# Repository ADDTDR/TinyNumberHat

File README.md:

# TinyNumberHat 

<!-- 

  -->

Red ALS314         |  Green AL304V 
:-------------------------:|:-------------------------:
  |  
                                                | 
<hr>
Clock example

<!-- # Build  -->

<!--img src="images/IMG_4520.jpeg" width="400"/-->

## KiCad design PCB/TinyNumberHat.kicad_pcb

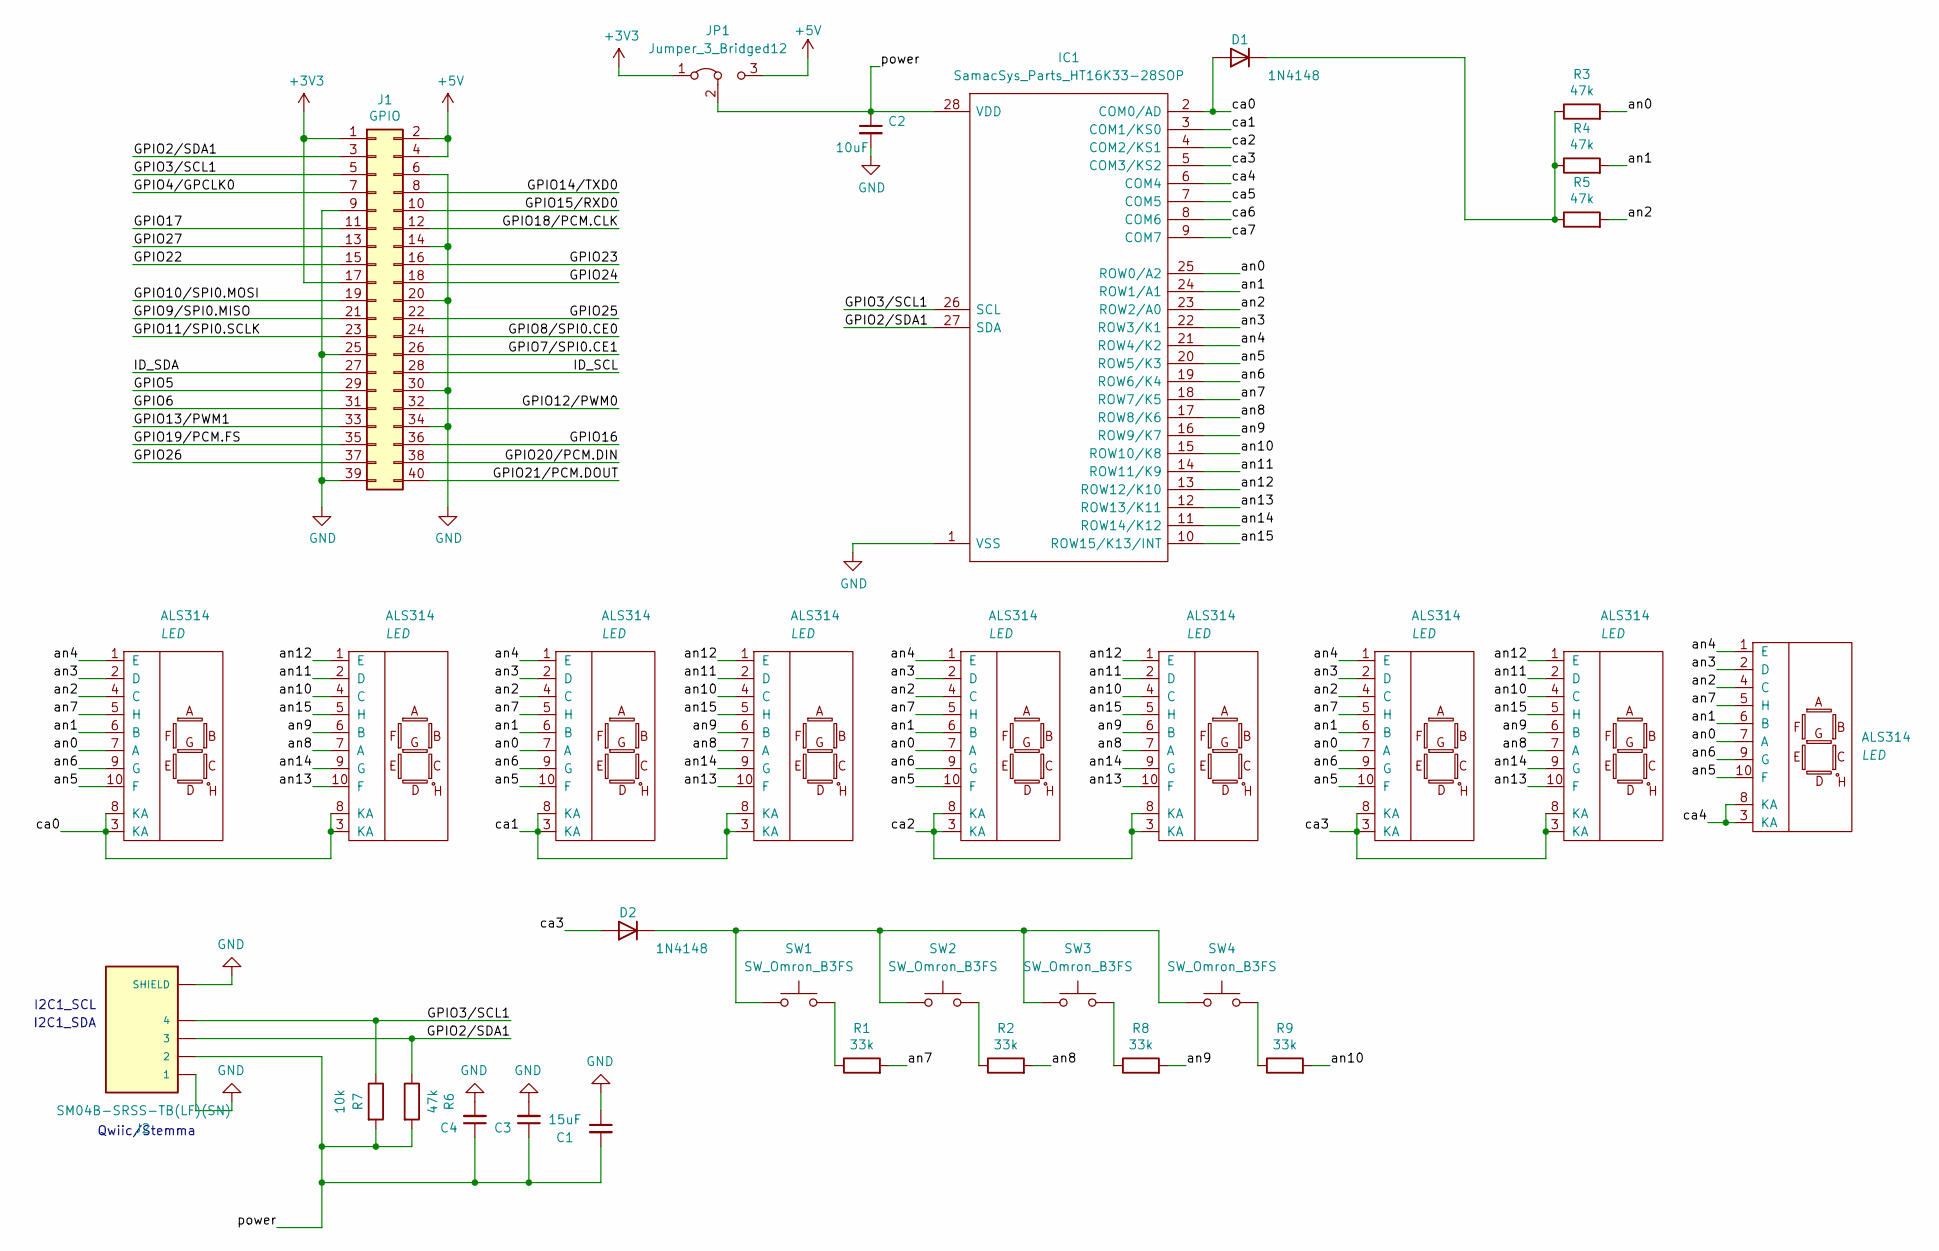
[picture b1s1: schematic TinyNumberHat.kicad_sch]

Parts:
C1: 15uF; C_1210_3225Metric_Pad1.33x2.70mm_HandSolder
C2, C3, C4: 10uF; C_0603_1608Metric
D1, D2: 1N4148; D_0805_2012Metric_Pad1.15x1.40mm_HandSolder
DPY1, DPY2, DPY3, DPY4, DPY5, DPY6, DPY7, DPY8, DPY9: ALS314
IC1: SamacSys_Parts_HT16K33-28SOP; SOIC127P1031X264-28N; Manufacturer_Part_Number HT16K33-28SOP
J1: GPIO; PinSocket_2x20_P2.54mm_Vertical
J2: SM04B-SRSS-TB(LF)(SN); JST_SM04B-SRSS-TB(LF)(SN); MPN SM04B-SRSS-TB(LF)(SN); Digi-Key_PN 455-1804-1-ND
JP1: Jumper_3_Bridged12; SolderJumper-3_P1.3mm_Bridged12_Pad1.0x1.5mm
R1, R2, R8, R9: 33k; R_0603_1608Metric
R3, R4, R5, R6: 47k; R_0603_1608Metric
R7: 10k; R_0603_1608Metric
SW1, SW2, SW3, SW4: SW_Omron_B3FS; SW_SPST_Omron_B3FS-105xP

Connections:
+3V3: J1.1, J1.17, JP1.1 (A)
+5V: J1.2, J1.4, JP1.3 (B)
/GPIO2/SDA1: IC1.27 (SDA), J1.3, J2.3, R6.1
/GPIO3/SCL1: IC1.26 (SCL), J1.5, J2.4, R7.1
/GPIO4/GPCLK0: J1.7
/GPIO5: J1.29
/GPIO6: J1.31
/GPIO7/SPI0.CE1: J1.26
/GPIO8/SPI0.CE0: J1.24
/GPIO9/SPI0.MISO: J1.21
/GPIO10/SPI0.MOSI: J1.19
/GPIO11/SPI0.SCLK: J1.23
/GPIO12/PWM0: J1.32
/GPIO13/PWM1: J1.33
/GPIO14/TXD0: J1.8
/GPIO15/RXD0: J1.10
/GPIO16: J1.36
/GPIO17: J1.11
/GPIO18/PCM.CLK: J1.12
/GPIO19/PCM.FS: J1.35
/GPIO20/PCM.DIN: J1.38
/GPIO21/PCM.DOUT: J1.40
/GPIO22: J1.15
/GPIO23: J1.16
/GPIO24: J1.18
/GPIO25: J1.22
/GPIO26: J1.37
/GPIO27: J1.13
/ID_SCL: J1.28
/ID_SDA: J1.27
/an0: DPY1.7 (A), DPY3.7 (A), DPY5.7 (A), DPY7.7 (A), DPY9.7 (A), IC1.25 (ROW0/A2), R3.2
/an1: DPY1.6 (B), DPY3.6 (B), DPY5.6 (B), DPY7.6 (B), DPY9.6 (B), IC1.24 (ROW1/A1), R4.2
/an2: DPY1.4 (C), DPY3.4 (C), DPY5.4 (C), DPY7.4 (C), DPY9.4 (C), IC1.23 (ROW2/A0), R5.2
/an3: DPY1.2 (D), DPY3.2 (D), DPY5.2 (D), DPY7.2 (D), DPY9.2 (D), IC1.22 (ROW3/K1)
/an4: DPY1.1 (E), DPY3.1 (E), DPY5.1 (E), DPY7.1 (E), DPY9.1 (E), IC1.21 (ROW4/K2)
/an5: DPY1.10 (F), DPY3.10 (F), DPY5.10 (F), DPY7.10 (F), DPY9.10 (F), IC1.20 (ROW5/K3)
/an6: DPY1.9 (G), DPY3.9 (G), DPY5.9 (G), DPY7.9 (G), DPY9.9 (G), IC1.19 (ROW6/K4)
/an7: DPY1.5 (H), DPY3.5 (H), DPY5.5 (H), DPY7.5 (H), DPY9.5 (H), IC1.18 (ROW7/K5), R1.2
/an8: DPY2.7 (A), DPY4.7 (A), DPY6.7 (A), DPY8.7 (A), IC1.17 (ROW8/K6), R2.2
/an9: DPY2.6 (B), DPY4.6 (B), DPY6.6 (B), DPY8.6 (B), IC1.16 (ROW9/K7), R8.2
/an10: DPY2.4 (C), DPY4.4 (C), DPY6.4 (C), DPY8.4 (C), IC1.15 (ROW10/K8), R9.2
/an11: DPY2.2 (D), DPY4.2 (D), DPY6.2 (D), DPY8.2 (D), IC1.14 (ROW11/K9)
/an12: DPY2.1 (E), DPY4.1 (E), DPY6.1 (E), DPY8.1 (E), IC1.13 (ROW12/K10)
/an13: DPY2.10 (F), DPY4.10 (F), DPY6.10 (F), DPY8.10 (F), IC1.12 (ROW13/K11)
/an14: DPY2.9 (G), DPY4.9 (G), DPY6.9 (G), DPY8.9 (G), IC1.11 (ROW14/K12)
/an15: DPY2.5 (H), DPY4.5 (H), DPY6.5 (H), DPY8.5 (H), IC1.10 (ROW15/K13/INT)
/ca0: D1.2 (A), DPY1.3 (KA), DPY1.8 (KA), DPY2.3 (KA), DPY2.8 (KA), IC1.2 (COM0/AD)
/ca1: DPY3.3 (KA), DPY3.8 (KA), DPY4.3 (KA), DPY4.8 (KA), IC1.3 (COM1/KS0)
/ca2: DPY5.3 (KA), DPY5.8 (KA), DPY6.3 (KA), DPY6.8 (KA), IC1.4 (COM2/KS1)
/ca3: D2.2 (A), DPY7.3 (KA), DPY7.8 (KA), DPY8.3 (KA), DPY8.8 (KA), IC1.5 (COM3/KS2)
/ca4: DPY9.3 (KA), DPY9.8 (KA), IC1.6 (COM4)
/ca5: IC1.7 (COM5)
/ca6: IC1.8 (COM6)
/ca7: IC1.9 (COM7)
/power: C1.2, C2.1, C3.1, C4.1, IC1.28 (VDD), J2.2, JP1.2 (C), R6.2, R7.2
GND: C1.1, C2.2, C3.2, C4.2, IC1.1 (VSS), J1.6, J1.9, J1.14, J1.20, J1.25, J1.30, J1.34, J1.39, J2.1, J2.S1 (SHIELD), J2.S2 (SHIELD)
unnamed: D1.1 (K), R3.1, R4.1, R5.1
unnamed: D2.1 (K), SW1.1, SW2.1, SW3.1, SW4.1
unnamed: R1.1, SW1.2
unnamed: R2.1, SW2.2
unnamed: R8.1, SW3.2
unnamed: R9.1, SW4.2

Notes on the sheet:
I2C1_SCL
I2C1_SDA
Qwiic/Stemma

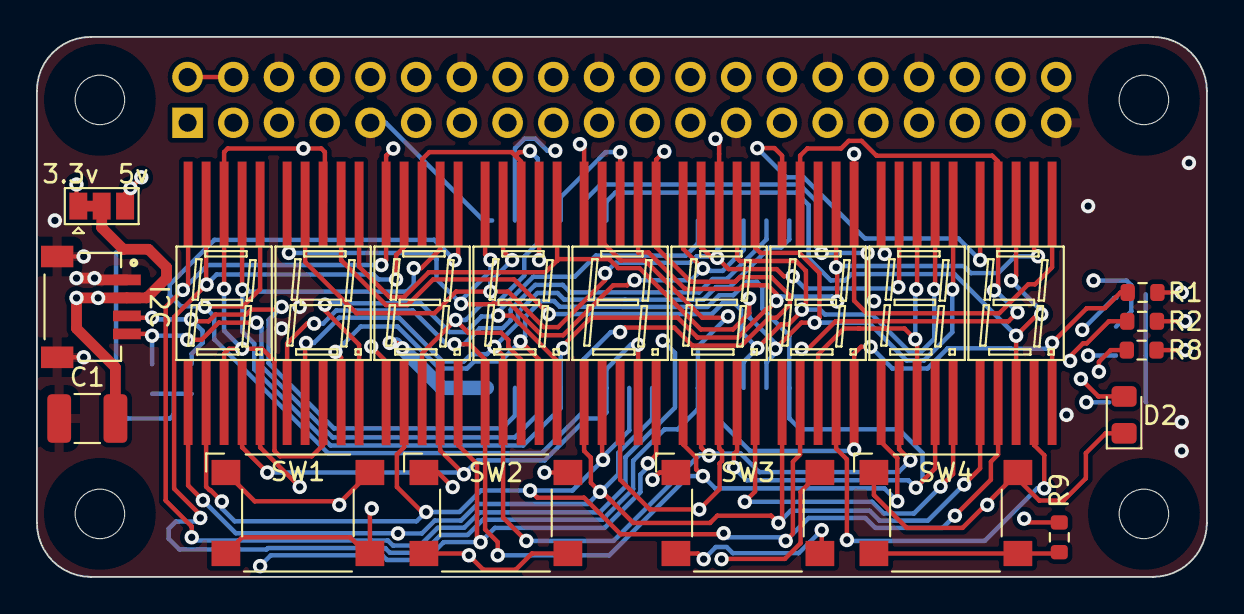
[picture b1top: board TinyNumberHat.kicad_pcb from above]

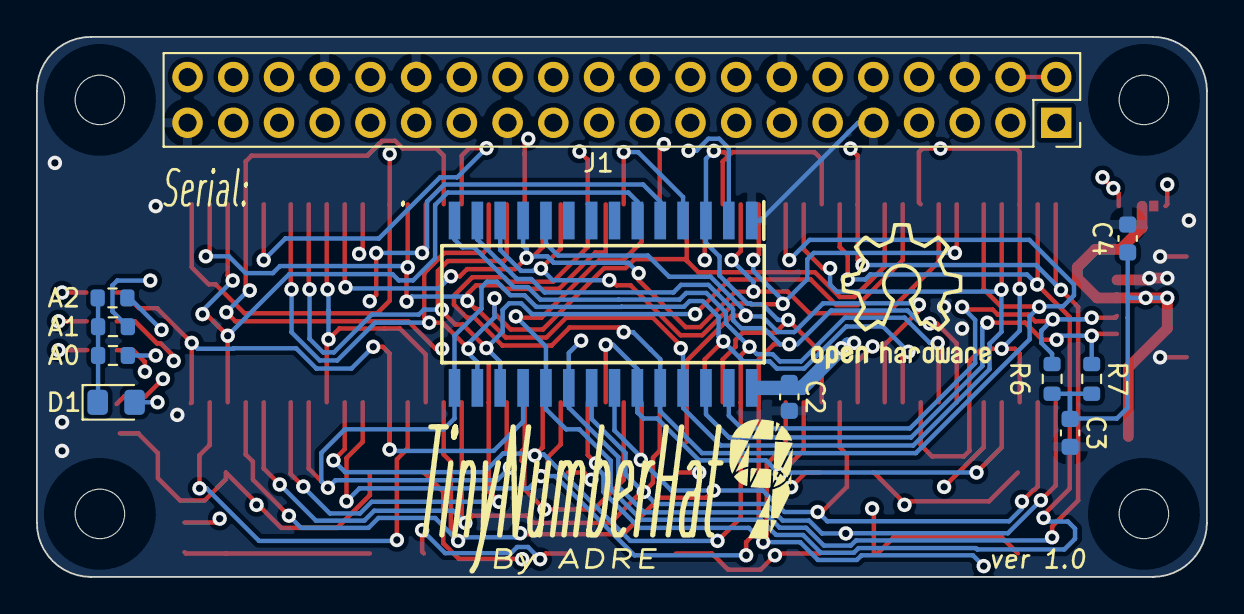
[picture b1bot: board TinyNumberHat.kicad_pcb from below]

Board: 4 copper layers, 65.0 x 30.0 mm, 32 parts (11 on the bottom side), 33 nets.

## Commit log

2023-11-03 Version 1.0
2023-11-13 Update silkscreens
2023-11-13 Update read me
2023-11-13 Update renders
2023-11-14 Minor updates
2023-11-17 Small updates
2023-12-03 Add images
2023-12-15 Add arduino sketch
2023-12-15 Update pcb
2023-12-27 Add arduino gps clock usage example, and python sketch
2023-12-27 Add minimal gps clock from gnrmc sence implementation for stm32g0 mcu
2023-12-27 Use unsorted map
2024-02-03 Remove mov files
2024-02-26 Show text
2024-02-27 Add few leters
2024-07-30 Update arduino sketch
2025-03-15 Update images
2025-03-15 Update to Kicad 9, add schematic
2025-03-19 Add bom file
